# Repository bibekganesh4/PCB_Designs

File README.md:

# PCB Designs - By BIBEK KUMAR GANESH

Welcome to the "PCB-Designs" repository, where electronics enthusiasts and hobbyists can explore a curated collection of printed circuit board (PCB) designs that will ignite their passion for DIY projects.

## Explore a World of Possibilities

Within this digital treasure trove, you'll discover a meticulously crafted array of PCB designs, each one a testament to the ingenuity and dedication of its creator. These designs are not mere schematics; they are the blueprints that breathe life into your electronic endeavors, transforming concepts into tangible reality.

Delve into the repository, and you'll find a diverse range of projects, from simple yet ingenious creations to complex masterpieces that challenge the boundaries of innovation. Whether you're a seasoned maker or a budding enthusiast, this repository promises to fuel your curiosity and inspire you to push the limits of your creativity.

## A Collaborative Journey

But this repository is more than just a collection of designs – it's a living, breathing community where ideas are shared, knowledge is disseminated, and collaboration flourishes. Engage with like-minded individuals, exchange insights, and contribute your own designs to this ever-evolving repository, leaving your mark on the world of DIY electronics.

## Unleash Your Creativity

So, embrace the adventure, unleash your creativity, and let the "PCB-Designs" repository be your guide in the captivating realm of printed circuit board design. Together, we'll embark on a journey of discovery, innovation, and boundless possibilities.

Join us today and let your imagination take flight!

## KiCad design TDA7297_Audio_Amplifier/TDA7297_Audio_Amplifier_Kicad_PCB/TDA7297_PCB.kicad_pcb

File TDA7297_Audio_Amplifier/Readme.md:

## TDA7297 Audio Amplifier PCB (KICAD)

Immerse yourself in the realm of crystal-clear audio with this meticulously designed PCB for the TDA7297 Audio Amplifier. Crafted with precision and attention to detail, this PCB promises to elevate your audio experience to new heights.

### About TDA7297

The TDA7297 is a monolithic integrated circuit designed for high-performance audio amplification. Featuring advanced technologies, it delivers exceptional sound quality with low distortion and high efficiency. This versatile amplifier boasts the following specifications:

- Output Power: 30W (RMS) into 4Ω load
- Wide Supply Voltage Range: 6V to 18V
- High Slew Rate: 20V/μs
- Low Quiescent Current: 60mA (typ.)
- Low Noise and Distortion: THD = 0.04% (typ.)

### Features

- Robust and compact PCB design optimized for the TDA7297 audio amplifier IC
- Comprehensive layout adhering to best practices for optimal signal integrity
- Carefully placed components and well-organized traces for efficient heat dissipation
- Provision for easy integration with external components and power supply
- Designed with KiCad, the open-source electronics design automation suite

### Applications

This PCB is an ideal solution for a wide range of audio applications, including:

- High-fidelity audio systems
- Portable speakers and amplifiers
- Multimedia setups
- Automotive audio systems
- Home theater systems
- Guitar amplifiers
- DIY audio projects

### Getting Started

To get started with this PCB design, simply clone or download the repository. The design files are compatible with KiCad, ensuring seamless integration and modification capabilities.

**Clone the Repository**: 
   ```bash
   git clone https://github.com/yourusername/TDA7297-Audio-Amplifier.git
   ```

Feel free to customize and adapt this design to suit your specific requirements. Whether you're an experienced maker or a curious beginner, this PCB design offers a solid foundation for your audio amplifier projects.

Join the community, share your experiences, and contribute your own enhancements to make this design even better!

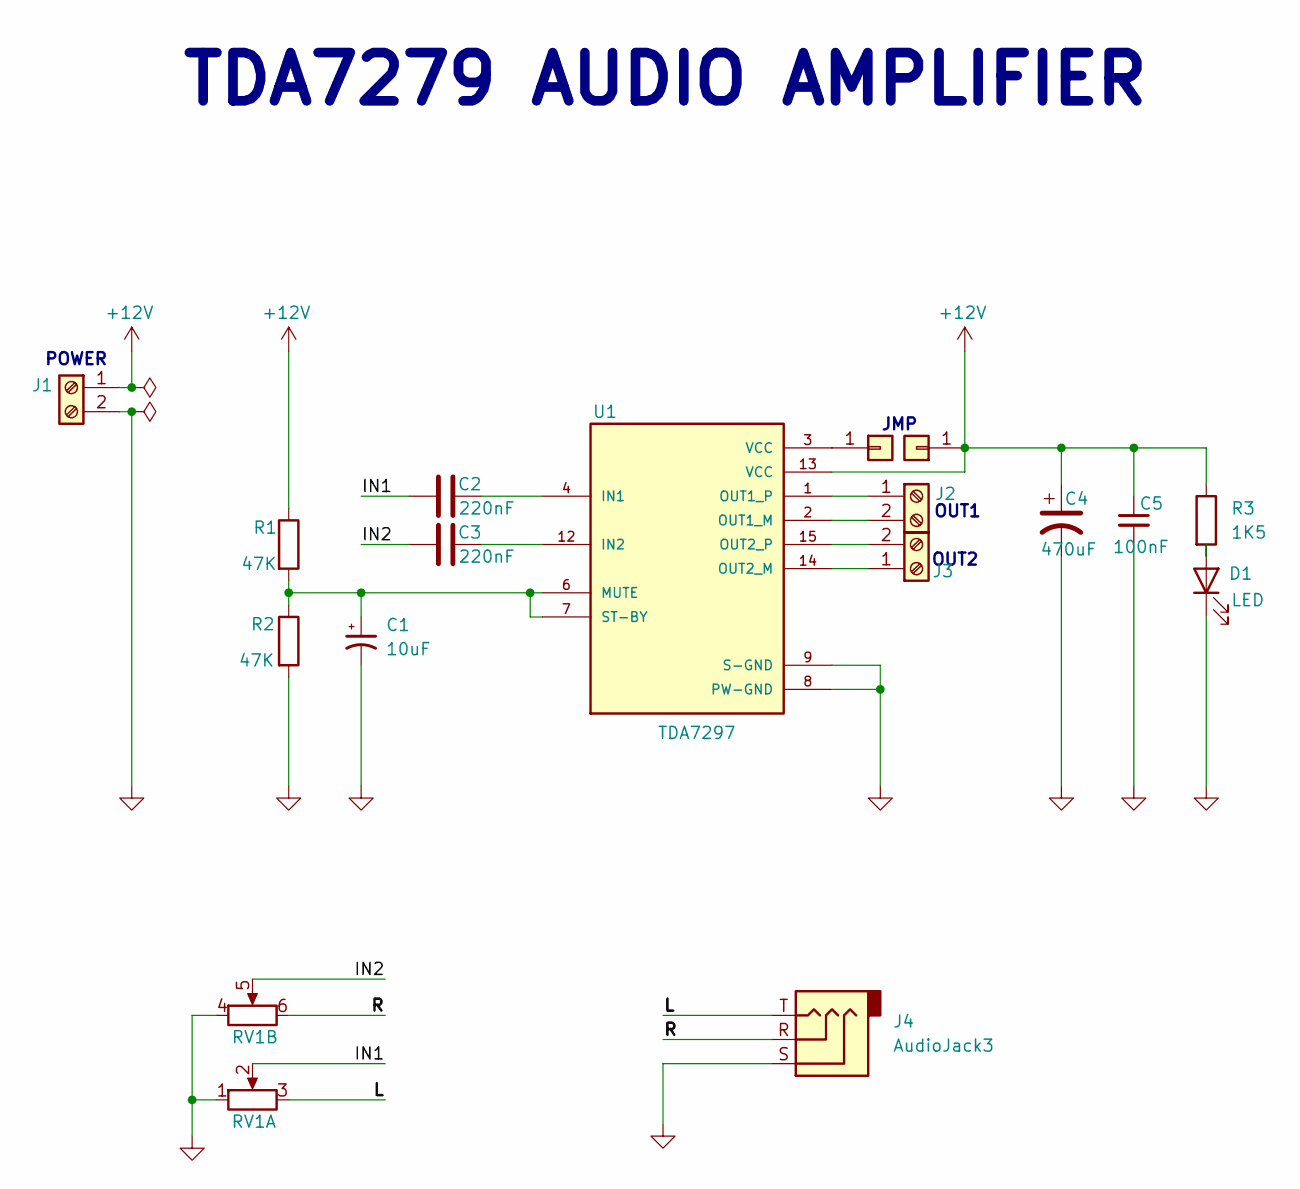
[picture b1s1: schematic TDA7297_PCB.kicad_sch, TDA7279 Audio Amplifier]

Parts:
C1: 10uF; CP_Radial_D5.0mm_P2.50mm
C2, C3: 220nF; C_Disc_D8.0mm_W2.5mm_P5.00mm
C4: 470uF; CP_Radial_D13.0mm_P5.00mm
C5: 100nF; C_Disc_D3.8mm_W2.6mm_P2.50mm
D1: LED; LED_D5.0mm
J1, J2, J3: Screw_Terminal_01x02; TerminalBlock_MetzConnect_Type094_RT03502HBLU_1x02_P5.00mm_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
J4: AudioJack3; Jack_3.5mm_CUI_SJ1-3523N_Horizontal
J5, J6: Conn_01x01; PinHeader_1x01_P1.00mm_Vertical
R1, R2: 47K; R_Axial_DIN0207_L6.3mm_D2.5mm_P10.16mm_Horizontal
R3: 1K5; R_Axial_DIN0207_L6.3mm_D2.5mm_P10.16mm_Horizontal
RV1: Potentiometer_Dual_Separate; Potentiometer_Alps_RK163_Dual_Horizontal
U1: TDA7297; TO127P2020X500X2100-15

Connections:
+12V: C4.1, C5.1, J1.1, J6.1, R1.1, R3.1, U1.13 (VCC)
/IN1: C2.1, RV1.2
/IN2: C3.1, RV1.5
/L: J4.T, RV1.3
/R: J4.R, RV1.6
GND: C1.2, C4.2, C5.2, D1.1 (K), J1.2, J4.S, R2.2, RV1.1, RV1.4, U1.8 (PW-GND), U1.9 (S-GND)
unnamed: D1.2 (A), R3.2
unnamed: J2.1, U1.1 (OUT1_P)
unnamed: J2.2, U1.2 (OUT1_M)
unnamed: J3.1, U1.14 (OUT2_M)
unnamed: J3.2, U1.15 (OUT2_P)
unnamed: J5.1, U1.3 (VCC)
unnamed: C2.2, U1.4 (IN1)
unnamed: C3.2, U1.12 (IN2)
unnamed: C1.1, R1.2, R2.1, U1.6 (MUTE), U1.7 (ST-BY)

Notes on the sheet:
TDA7279 AUDIO AMPLIFIER
OUT1
OUT2
POWER
JMP

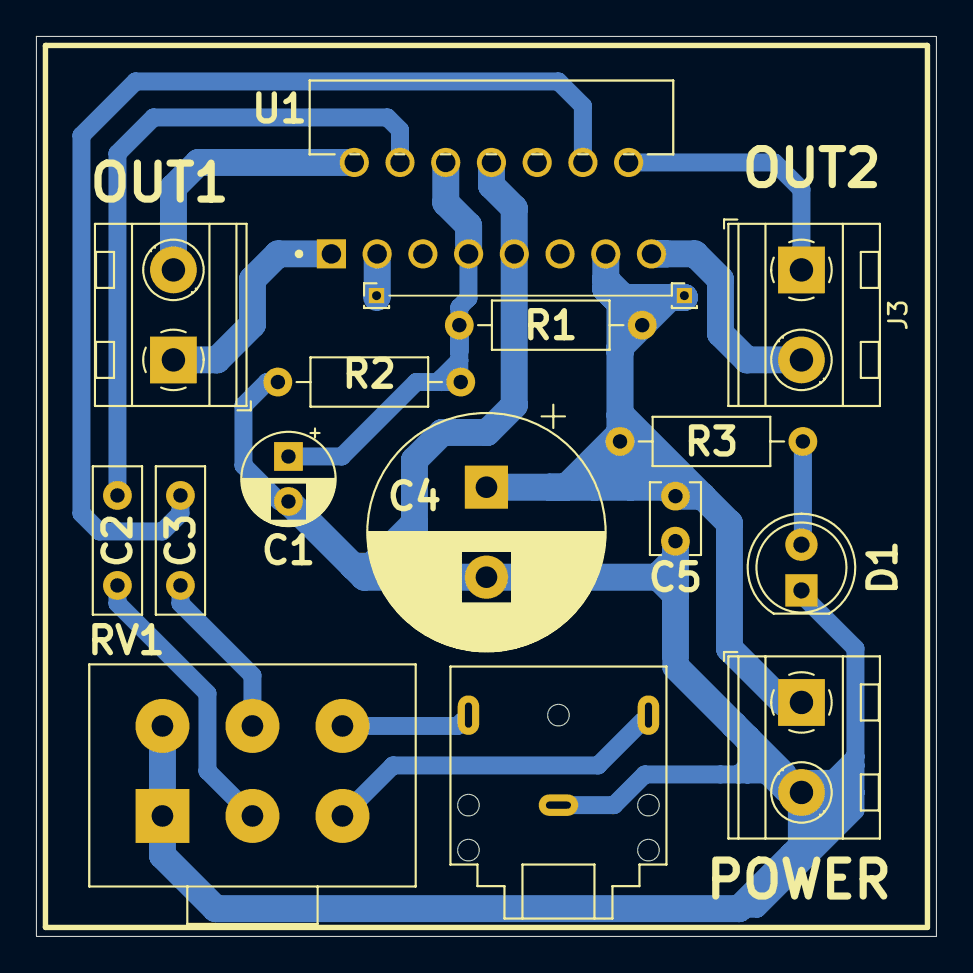
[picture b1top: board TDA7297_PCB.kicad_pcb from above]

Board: 2 copper layers, 50.0 x 50.0 mm, 17 parts (0 on the bottom side), 15 nets.

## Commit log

2024-06-17 Create hi
2024-06-17 Create k
2024-06-17 Create l
